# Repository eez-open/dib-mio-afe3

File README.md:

### Ownership and License
The contributors are listed in CONTRIB.TXT.

Licenses | OSHWA UID
--|--
 | 

### Overview

The [EEZ DIB](https://github.com/eez-open/modular-psu) 4-channel Hi-voltage/Hi-current AFE for [MIO168](https://github.com/eez-open/dib-mio168) module with two isolated inputs for voltage and current measurements.

### Feature list
* [ADS131E04](https://www.ti.com/product/ADS131E04) 24-bit 4-channel simultaneous sampling ADC with SPI
* AIN#1: Hi-voltage isolated (floated) input featuring 2 measurement ranges (±50 V, ±450 V)
* AIN#2: Hi-current isolated (floated) input featuring 2 measurement ranges (±1 A, ±10 A)
* AIN#3: Hi-voltage input featuring 3 measurement ranges (±2.4 V, ±48 V, ±240 V)
* AIN#4: Hi-current input featuring 3 measurement ranges (±24 mA, ±1.2 A, ±10 A), share common GND with AIN#3
* Latching relays for lower continuous power consumption
* Fused current inputs
* On-board ±2.5 V low noise LDOs
* Optional external voltage reference
* Dimensions: 132 x 68.5 mm, 4-layer PCB

### r1B4 prototype 3D model

### KiCad project (v7 or newer)

* [AFE3 r1B4](https://github.com/eez-open/dib-mio-afe3/tree/master/EDA%20files/KiCad)

All symbols, footprints and 3D models used in the project can be found in the [EEZ-DIB Library](https://github.com/eez-open/eez-kicad-libraries) plugin for KiCad.

### Bill of materials

* [Download](https://github.com/eez-open/dib-mio-afe3/tree/master/EDA%20files/KiCad/bom/ibom.html) as raw file _Interactive BOM_ (ibom.html) and open it locally in your browser.

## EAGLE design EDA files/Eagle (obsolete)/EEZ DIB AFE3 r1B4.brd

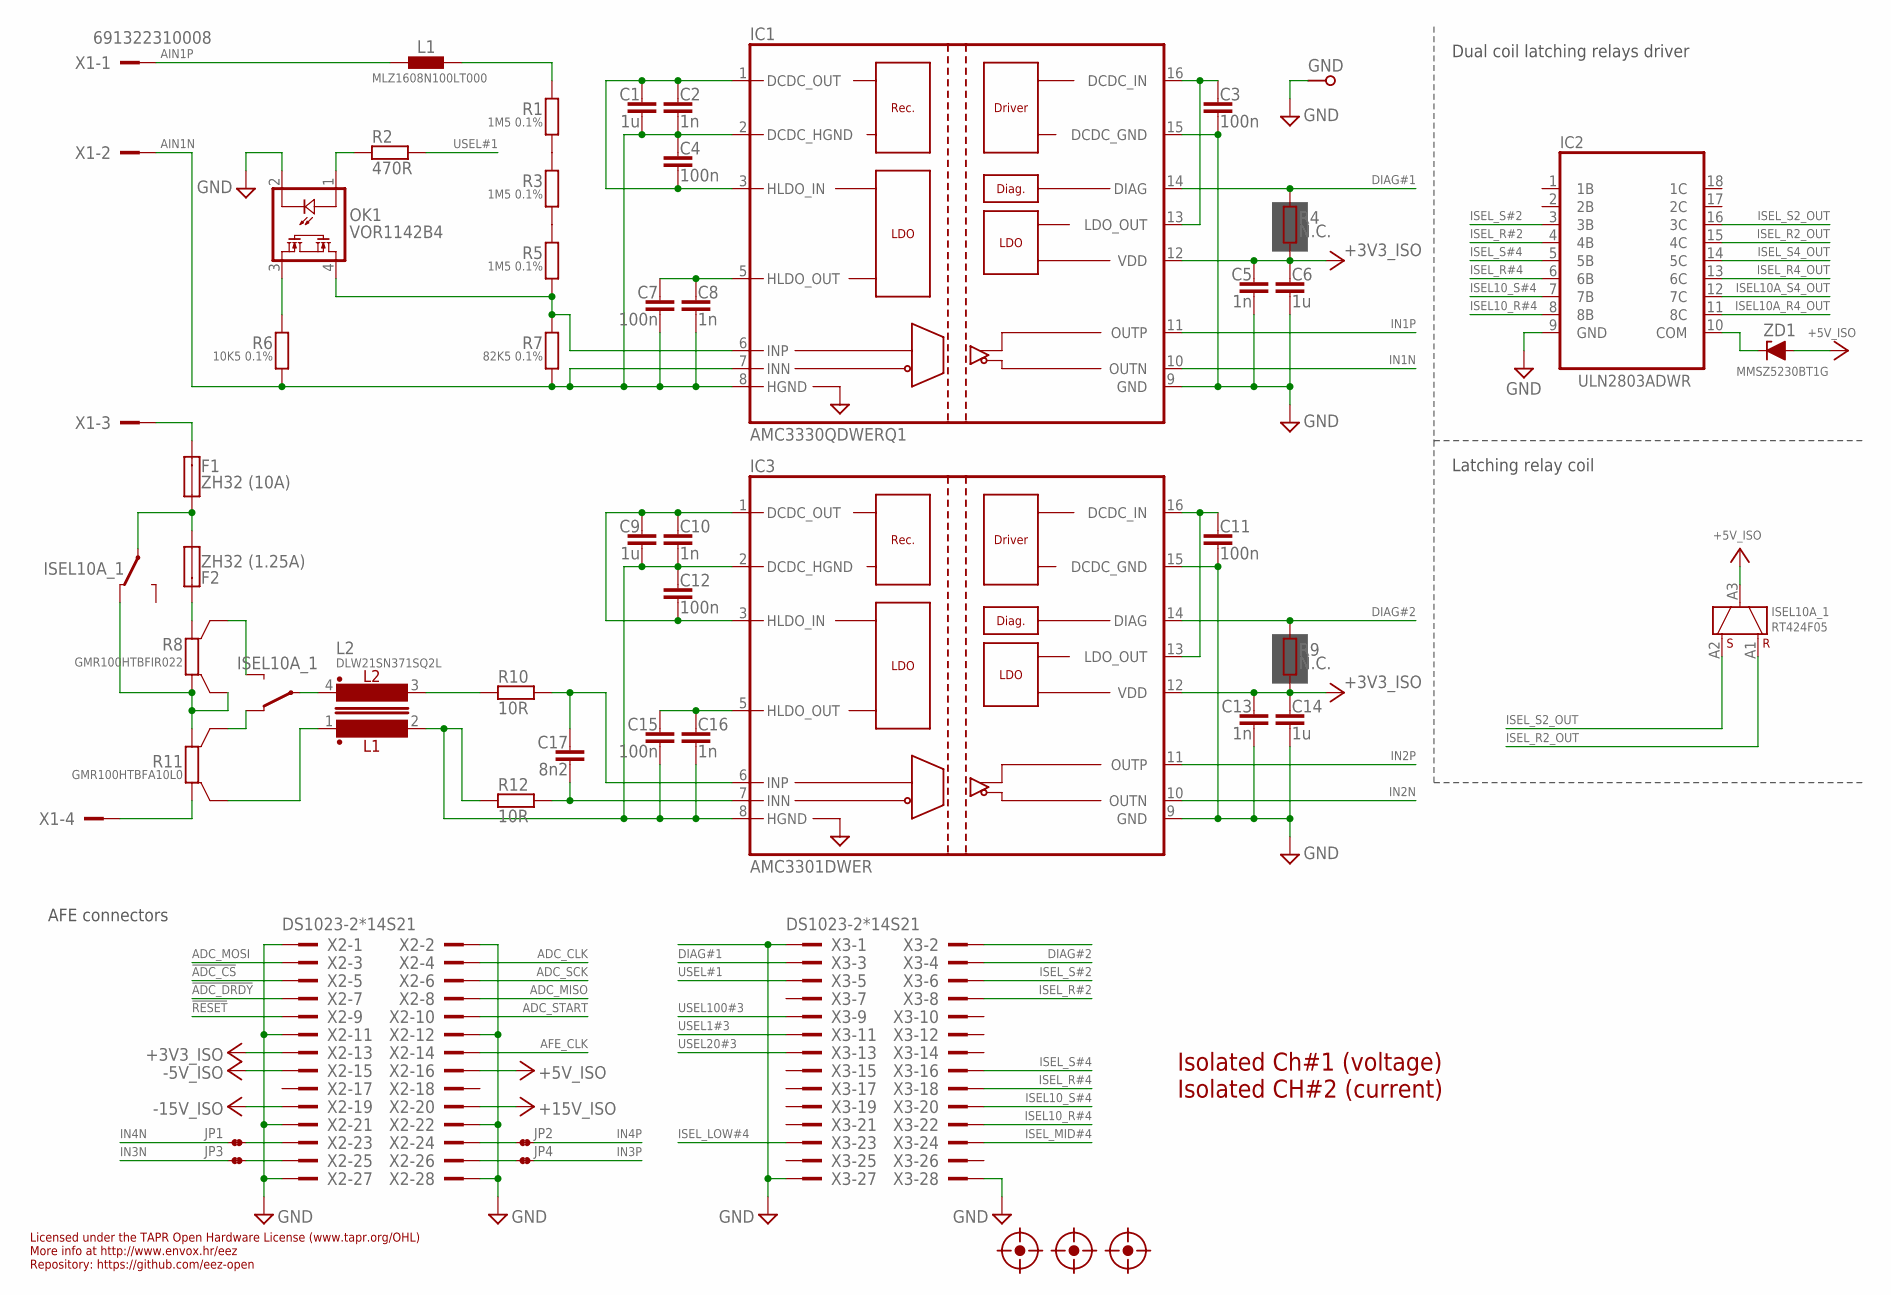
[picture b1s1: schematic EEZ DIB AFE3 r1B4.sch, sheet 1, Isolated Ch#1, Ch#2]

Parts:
C1, C9: 1u; C0603
C2, C10: 1n; C0603
C3, C4, C11, C12: 100n; C0603
C5, C8, C13, C16: 1n; C1206
C6, C14: 1u; C1206
C7, C15: 100n; C1206
C17: 8n2; C0603
F1: ZH32 (10A); ZH32
F2: ZH32 (1.25A); ZH32
FM1, FM2, FM3: FIDUCIAL_2; FIDUCIAL_DUAL
GND: PCB_TEST_TABSHIELD; PCB_SHIELD_TAB
IC1: AMC3330QDWERQ1; DW16
IC2: ULN2803ADWR; DW18_TEX-M
IC3: AMC3301DWER; DW16
ISEL10A_1: RT424F05; RT424FXX
JP1, JP2, JP3, JP4: JP2-NOCUT-0805; JP2-0805-NOCUT
L1: MLZ1608N100LT000; BEAD0603
L2: DLW21SN371SQ2L; MURATA_DLW21S
OK1: VOR1142B4; DIL4-SMD
R1, R3, R5: 1M5 0.1%; R1206
R2: 470R; R0805
R4, R9: N.C.; R0805
R6: 10K5 0.1%; R1206
R7: 82K5 0.1%; R1206
R8: GMR100HTBFIR022; R_2512-4WIRE
R10, R12: 10R; R0805
R11: GMR100HTBFA10L0; R_2512-4WIRE
X1: 691322310008
X2, X3: DS1023-2*14S21; TSW-114-07-F-D
ZD1: MMSZ5230BT1G; SOD123

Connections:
!ADC_CS: X2.5; also elsewhere on the board
!ADC_DRDY: X2.7; also elsewhere on the board
!RESET: X2.9; also elsewhere on the board
+3V3_ISO: C5.1, C6.1, C13.1, C14.1, IC1.12 (VDD), IC3.12 (VDD), R4.2, R9.2, X2.13; also elsewhere on the board
+5V_ISO: ISEL10A_1.A3 (COM), X2.16, ZD1.A; also elsewhere on the board
+15V_ISO: X2.20; also elsewhere on the board
-5V_ISO: X2.15; also elsewhere on the board
-15V_ISO: X2.19; also elsewhere on the board
ADC_CLK: X2.4; also elsewhere on the board
ADC_MISO: X2.8; also elsewhere on the board
ADC_MOSI: X2.3; also elsewhere on the board
ADC_SCK: X2.6; also elsewhere on the board
ADC_START: X2.10; also elsewhere on the board
AFE_CLK: X2.14
AIN1N: C1.2, C2.2, C4.1, C7.2, C8.2, IC1.2 (DCDC_HGND), IC1.7 (INN), IC1.8 (HGND), R6.1, R7.1, X1.2
AIN1P: L1.P$2 (2), X1.1
AIN2N: R11.1, X1.4
AIN2P: F1.2, X1.3
DIAG#1: IC1.14 (DIAG), R4.1, X3.3
DIAG#2: IC3.14 (DIAG), R9.1, X3.4
GND: C3.2, C5.2, C6.2, C11.2, C13.2, C14.2, GND.1, IC1.9 (GND), IC1.15 (DCDC_GND), IC2.9 (GND), IC3.9 (GND), IC3.15 (DCDC_GND), OK1.2 (C), X2.1, X2.2, X2.11, X2.12, X2.21, X2.22, X2.27, X2.28, X3.1, X3.27, X3.28; also elsewhere on the board
GNDI1: C9.2, C10.2, C12.1, C15.2, C16.2, IC3.2 (DCDC_HGND), IC3.8 (HGND), L2.2, R12.2
HI_FORCE+: ISEL10A_1.12 (NC), R8.1, R8.1S, R11.2
HI_SENSE+: ISEL10A_1.22 (NC), R11.2S
IN1N: IC1.10 (OUTN); also elsewhere on the board
IN1P: IC1.11 (OUTP); also elsewhere on the board
IN2N: IC3.10 (OUTN); also elsewhere on the board
IN2P: IC3.11 (OUTP); also elsewhere on the board
IN3N: JP3.1; also elsewhere on the board
IN3P: JP4.2; also elsewhere on the board
IN4N: JP1.1; also elsewhere on the board
IN4P: JP2.2; also elsewhere on the board
ISEL10A_R4_OUT: IC2.11 (8C); also elsewhere on the board
ISEL10A_S4_OUT: IC2.12 (7C); also elsewhere on the board
ISEL10_R#4: IC2.8 (8B), X3.22
ISEL10_S#4: IC2.7 (7B), X3.20
ISEL_LOW#4: X3.23; also elsewhere on the board
ISEL_MID#4: X3.24; also elsewhere on the board
ISEL_R2_OUT: IC2.15 (4C), ISEL10A_1.A1 (R)
ISEL_R4_OUT: IC2.13 (6C); also elsewhere on the board
ISEL_R#2: IC2.4 (4B), X3.8
ISEL_R#4: IC2.6 (6B), X3.18
ISEL_S2_OUT: IC2.16 (3C), ISEL10A_1.A2 (S)
ISEL_S4_OUT: IC2.14 (5C); also elsewhere on the board
ISEL_S#2: IC2.3 (3B), X3.6
ISEL_S#4: IC2.5 (5B), X3.16
LOW_SENSE+: ISEL10A_1.24 (NO), R8.2S
LO_FORCE-: F2.2, R8.2
unnamed: L1.P$1 (1), R1.2
unnamed: IC1.6 (INP), OK1.4 (S1), R5.1, R7.2
unnamed: R1.1, R3.2
unnamed: R3.1, R5.2
unnamed: OK1.3 (S2), R6.2
unnamed: C1.1, C2.1, C4.2, IC1.1 (DCDC_OUT), IC1.3 (HLDO_IN)
unnamed: C7.1, C8.1, IC1.5 (HLDO_OUT)
unnamed: C3.1, IC1.13 (LDO_OUT), IC1.16 (DCDC_IN)
unnamed: C17.1, IC3.6 (INP), R10.1
unnamed: C9.1, C10.1, C12.2, IC3.1 (DCDC_OUT), IC3.3 (HLDO_IN)
unnamed: C15.1, C16.1, IC3.5 (HLDO_OUT)
unnamed: C11.1, IC3.13 (LDO_OUT), IC3.16 (DCDC_IN)
unnamed: ISEL10A_1.21 (COM), L2.4
unnamed: F1.1, F2.1, ISEL10A_1.11 (COM)
unnamed: L2.1, R11.1S
unnamed: OK1.1 (A), R2.1
unnamed: L2.3, R10.2
unnamed: C17.2, IC3.7 (INN), R12.1
unnamed: IC2.10 (COM), ZD1.C
unnamed: JP1.2, X2.23
unnamed: JP3.2, X2.25
unnamed: JP2.1, X2.24
unnamed: JP4.1, X2.26
USEL1#3: X3.11; also elsewhere on the board
USEL20#3: X3.13; also elsewhere on the board
USEL100#3: X3.9; also elsewhere on the board
USEL#1: R2.2, X3.5

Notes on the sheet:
Licensed under the TAPR Open Hardware License (www.tapr.org/OHL)
Repository: https://github.com/eez-open
More info at http://www.envox.hr/eez
Isolated Ch#1 (voltage) Isolated CH#2 (current)
AFE connectors
Dual coil latching relays driver
Latching relay coil

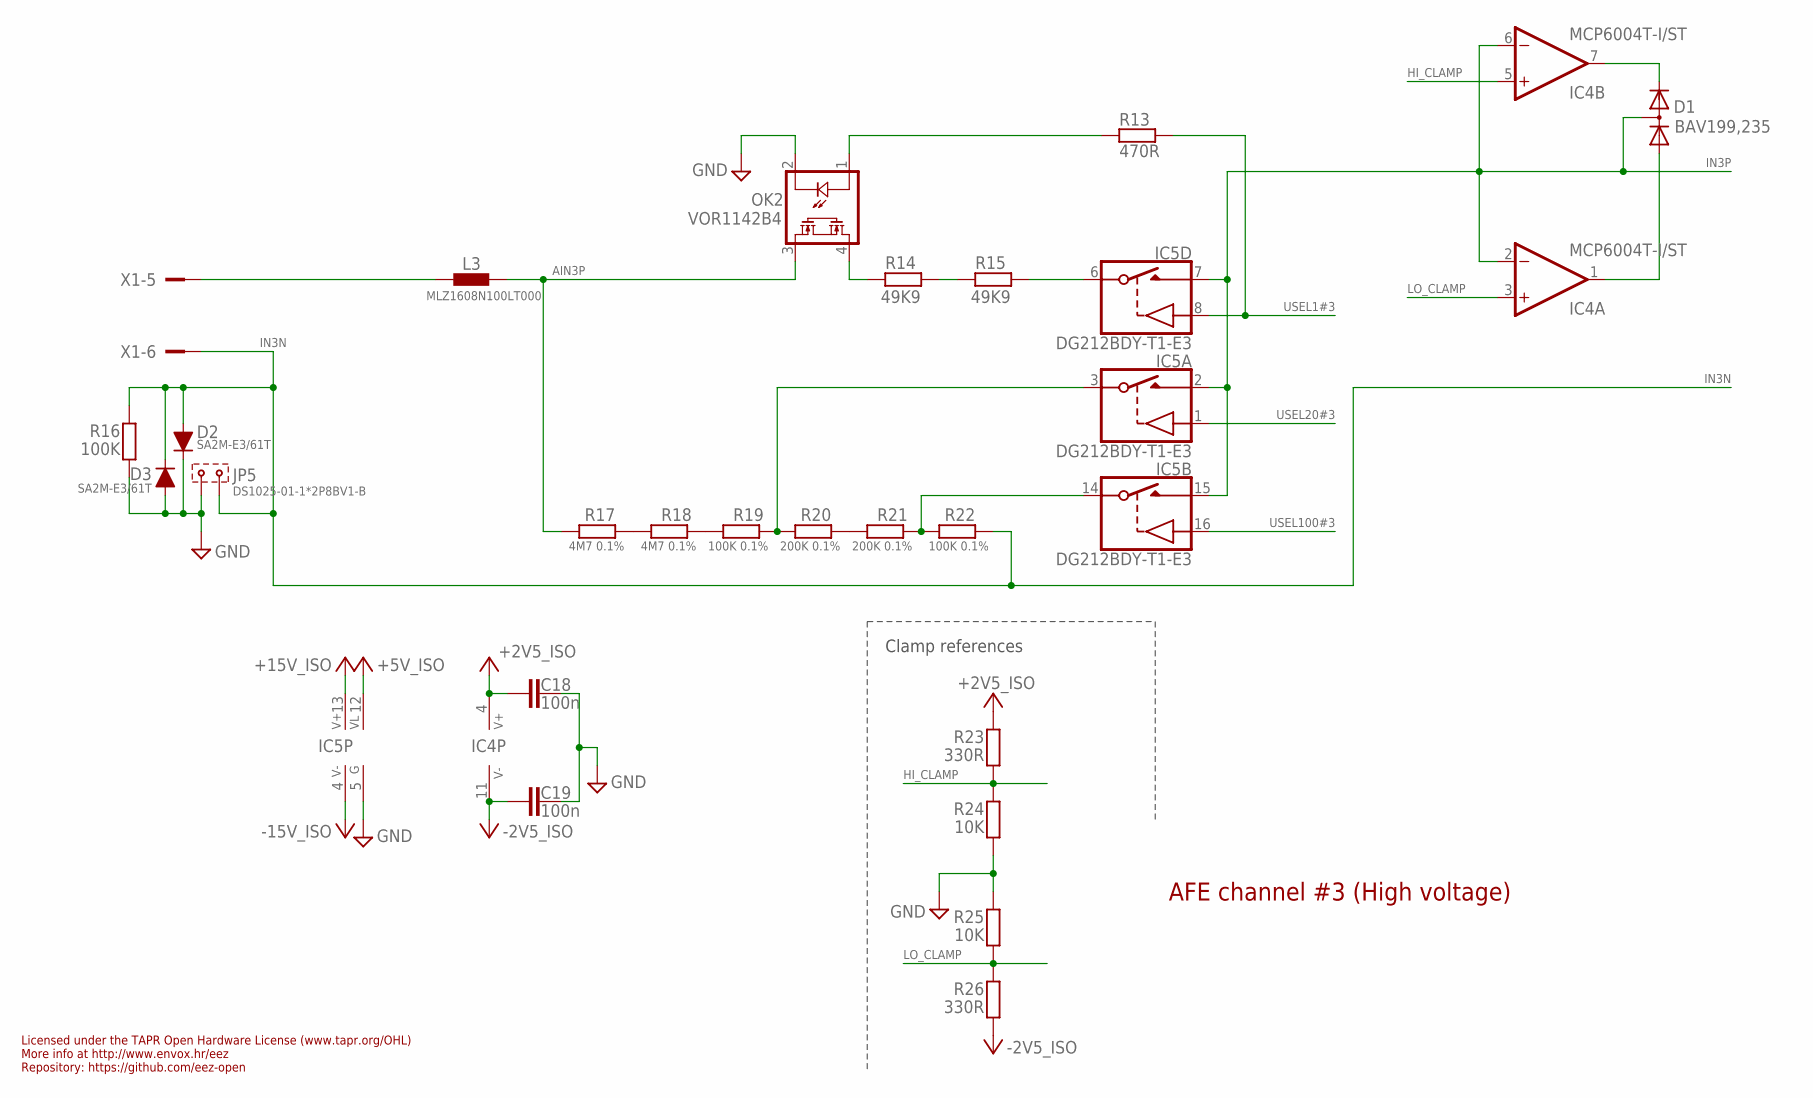
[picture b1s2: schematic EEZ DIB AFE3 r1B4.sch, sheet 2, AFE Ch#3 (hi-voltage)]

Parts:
C18, C19: 100n; C0603
D1: BAV199,235; SOT23
D2, D3: SA2M-E3/61T; SMA_NARROW
IC4: MCP6004T-I/ST; PW(R-PDSO-G14)
IC5: DG212BDY-T1-E3; SO16
JP5: DS1025-01-1*2P8BV1-B; 2MM-2
L3: MLZ1608N100LT000; BEAD0603
OK2: VOR1142B4; DIL4-SMD
R13: 470R; R0805
R14, R15: 49K9; R1206
R16: 100K; R1206
R17, R18: 4M7 0.1%; R1206
R19, R22: 100K 0.1%; R1206
R20, R21: 200K 0.1%; R1206
R23, R26: 330R; R0805
R24, R25: 10K; R0805
X1: 691322310008

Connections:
+2V5_ISO: C18.2, IC4.4 (V+), R23.1; also elsewhere on the board
+5V_ISO: IC5.12 (VL); also elsewhere on the board
+15V_ISO: IC5.13 (V+); also elsewhere on the board
-2V5_ISO: C19.2, IC4.11 (V-), R26.2; also elsewhere on the board
-15V_ISO: IC5.4 (V-); also elsewhere on the board
AIN3/20: IC5.3 (S), R19.1, R20.2
AIN3P: L3.P$1 (1), OK2.3 (S2), R17.2
GND: C18.1, C19.1, D2.1 (C), D3.2 (A), IC5.5 (GND), JP5.2, OK2.2 (C), R16.1, R24.2, R25.1; also elsewhere on the board
HI_CLAMP: IC4.5 (+IN), R23.2, R24.1; also elsewhere on the board
IN3N: D2.2 (A), D3.1 (C), JP5.1, R16.2, R22.1, X1.6; also elsewhere on the board
IN3P: D1.3 (AC), IC4.2 (-IN), IC4.6 (-IN), IC5.2 (D), IC5.7 (D), IC5.15 (D); also elsewhere on the board
LO_CLAMP: IC4.3 (+IN), R25.2, R26.1; also elsewhere on the board
unnamed: L3.P$2 (2), X1.5
unnamed: OK2.4 (S1), R14.2
unnamed: IC5.14 (S), R21.1, R22.2
unnamed: IC5.6 (S), R15.1
unnamed: D1.2 (C), IC4.7 (OUT)
unnamed: D1.1 (A), IC4.1 (OUT)
unnamed: R14.1, R15.2
unnamed: R20.1, R21.2
unnamed: R18.1, R19.2
unnamed: R17.1, R18.2
unnamed: OK2.1 (A), R13.2
USEL1#3: IC5.8 (IN), R13.1; also elsewhere on the board
USEL20#3: IC5.1 (IN); also elsewhere on the board
USEL100#3: IC5.16 (IN); also elsewhere on the board

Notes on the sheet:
Licensed under the TAPR Open Hardware License (www.tapr.org/OHL)
Repository: https://github.com/eez-open
More info at http://www.envox.hr/eez
AFE channel #3 (High voltage)
Clamp references

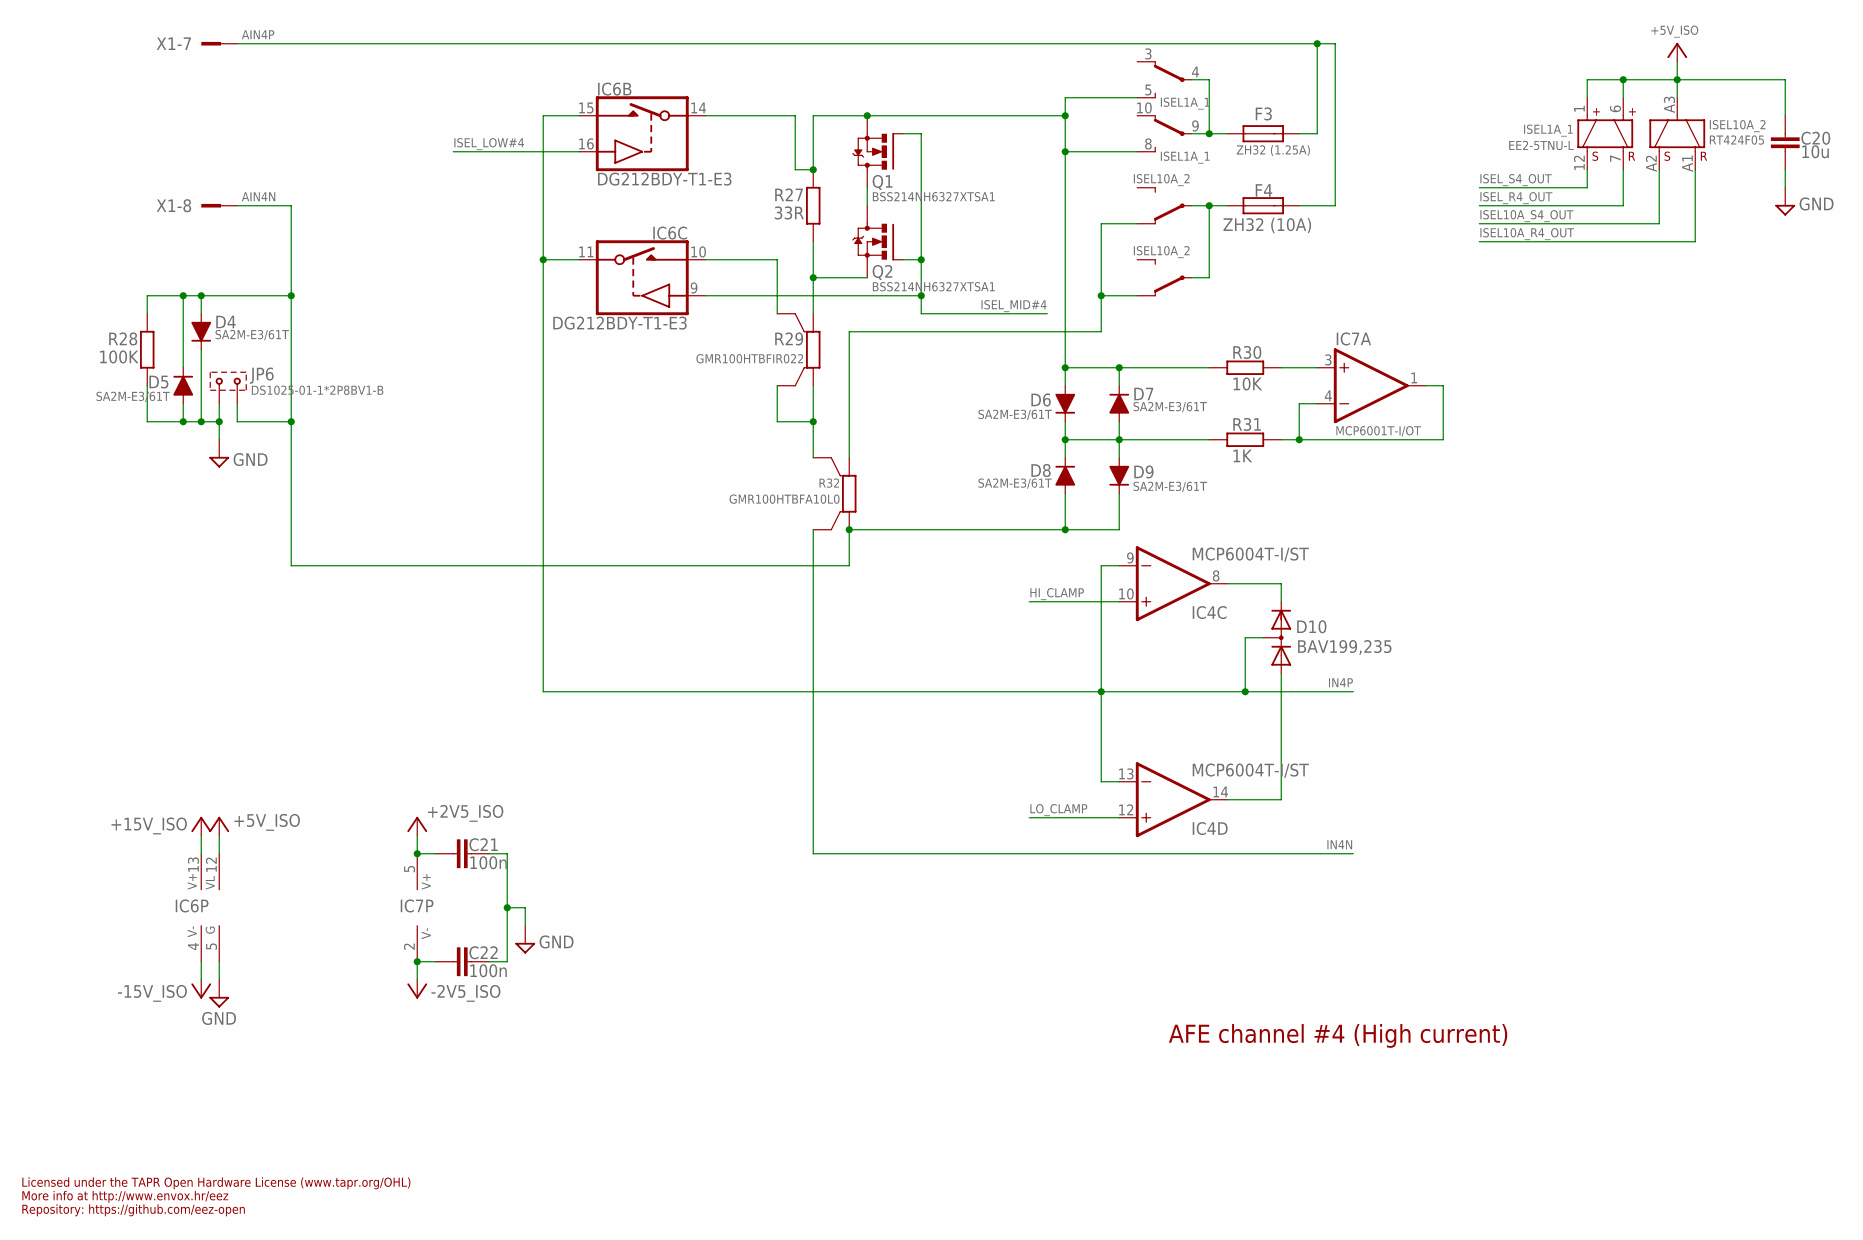
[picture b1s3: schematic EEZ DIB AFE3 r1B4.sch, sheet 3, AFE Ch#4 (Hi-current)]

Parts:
C20: 10u; C1206
C21, C22: 100n; C0603
D4, D5, D6, D7, D8, D9: SA2M-E3/61T; SMA_NARROW
D10: BAV199,235; SOT23
F3: ZH32 (1.25A); ZH32
F4: ZH32 (10A); ZH32
IC4: MCP6004T-I/ST; PW(R-PDSO-G14)
IC6: DG212BDY-T1-E3; SO16
IC7: MCP6001T-I/OT; DBV5
ISEL1A_1: EE2-5TNU-L; G6SK-2F
ISEL10A_2: RT424F05; RT424FXX
JP6: DS1025-01-1*2P8BV1-B; 2MM-2
Q1: BSS214NH6327XTSA1; SOT103P240X110-3N; MPN 2N7002-7-F
Q2: BSS214NH6327XTSA1; SOT103P240X110-3N
R27: 33R; R1206
R28: 100K; R1206
R29: GMR100HTBFIR022; R_2512-4WIRE
R30: 10K; R0805
R31: 1K; R0805
R32: GMR100HTBFA10L0; R_2512-4WIRE
X1: 691322310008

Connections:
+2V5_ISO: C21.2, IC7.5 (V+); also elsewhere on the board
+5V_ISO: C20.1, IC6.12 (VL), ISEL1A_1.1 (S+), ISEL1A_1.6 (R+), ISEL10A_2.A3 (COM); also elsewhere on the board
+15V_ISO: IC6.13 (V+); also elsewhere on the board
-2V5_ISO: C22.2, IC7.2 (V-); also elsewhere on the board
-15V_ISO: IC6.4 (V-); also elsewhere on the board
AIN4N: D4.2 (A), D5.1 (C), D8.2 (A), D9.1 (C), JP6.1, R28.2, R32.1, X1.8
AIN4P: F3.2, F4.2, X1.7
AIN4P_FUSED: F3.1, ISEL1A_1.4 (COM), ISEL1A_1.9 (COM)
GND: C20.2, C21.1, C22.1, D4.1 (C), D5.2 (A), IC6.5 (GND), JP6.2, R28.1; also elsewhere on the board
HI_CLAMP: IC4.10 (+IN); also elsewhere on the board
HI_CURR#1: ISEL10A_2.12 (NC), ISEL10A_2.22 (NC), R32.2
IN4N: R32.1S; also elsewhere on the board
IN4P: D10.3 (AC), IC4.9 (-IN), IC4.13 (-IN), IC6.11 (S), IC6.15 (D); also elsewhere on the board
ISEL10A_R4_OUT: ISEL10A_2.A1 (R); also elsewhere on the board
ISEL10A_S4_OUT: ISEL10A_2.A2 (S); also elsewhere on the board
ISEL_LOW#4: IC6.16 (IN); also elsewhere on the board
ISEL_MID#4: IC6.9 (IN), Q1.1 (G), Q2.1 (G); also elsewhere on the board
ISEL_R4_OUT: ISEL1A_1.7 (R-); also elsewhere on the board
ISEL_S4_OUT: ISEL1A_1.12 (S-); also elsewhere on the board
LO_CLAMP: IC4.12 (+IN); also elsewhere on the board
unnamed: R29.1, R29.1S, R32.2S
unnamed: IC6.10 (D), R29.2S
unnamed: F4.1, ISEL10A_2.11 (COM), ISEL10A_2.21 (COM)
unnamed: Q1.3 (D), Q2.3 (D)
unnamed: Q2.2 (S), R27.1, R29.2
unnamed: D6.1 (C), D7.2 (A), D8.1 (C), D9.2 (A), R31.2
unnamed: D6.2 (A), D7.1 (C), IC6.14 (S), ISEL1A_1.5 (NO), ISEL1A_1.8 (NO), Q1.2 (S), R27.2, R30.2
unnamed: IC7.1 (OUT), IC7.4 (-IN), R31.1
unnamed: IC7.3 (+IN), R30.1
unnamed: D10.2 (C), IC4.8 (OUT)
unnamed: D10.1 (A), IC4.14 (OUT)

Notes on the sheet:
Licensed under the TAPR Open Hardware License (www.tapr.org/OHL)
Repository: https://github.com/eez-open
More info at http://www.envox.hr/eez
AFE channel #4 (High current)

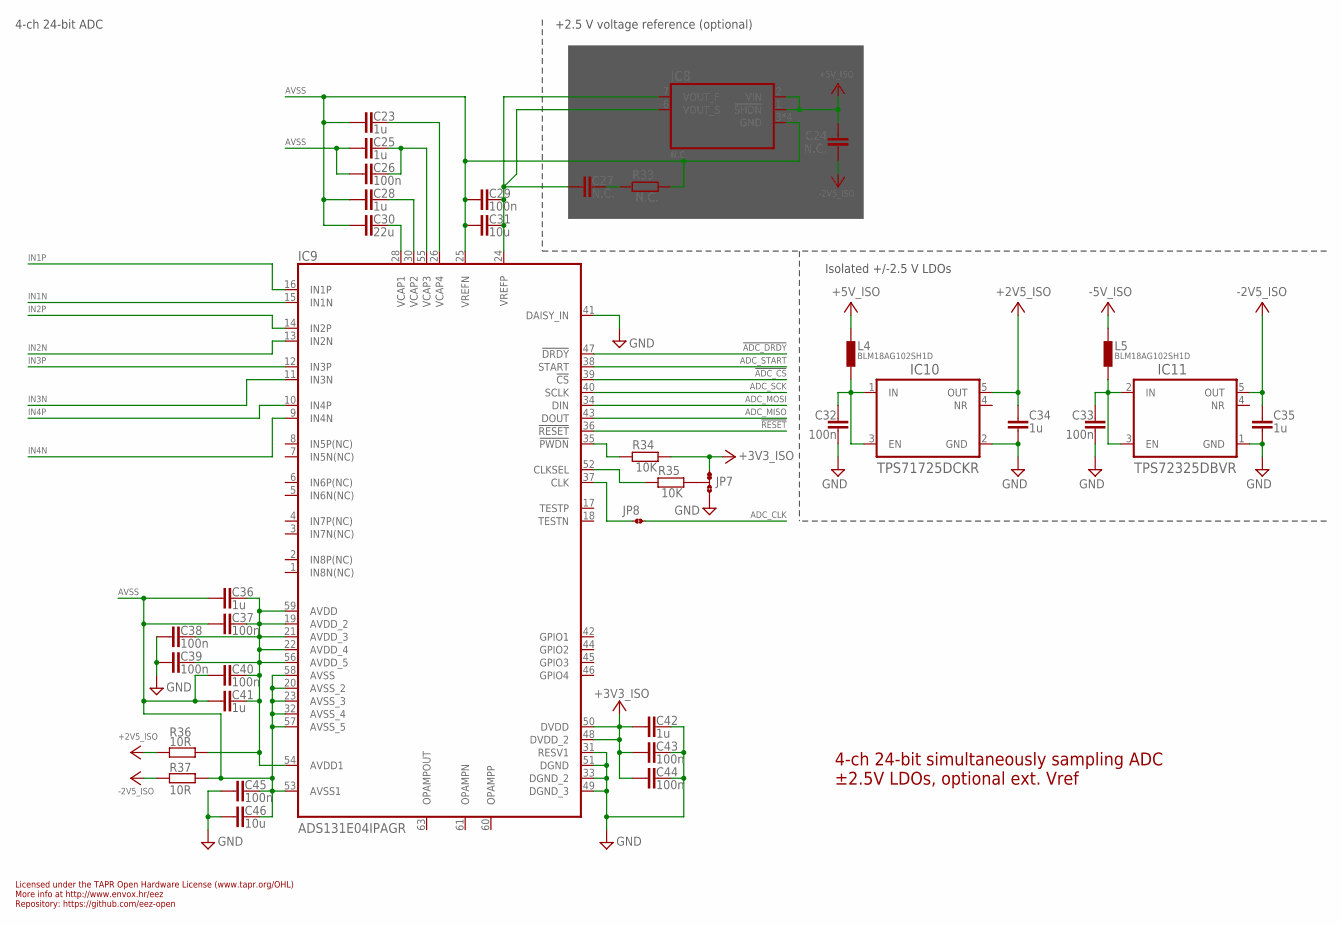
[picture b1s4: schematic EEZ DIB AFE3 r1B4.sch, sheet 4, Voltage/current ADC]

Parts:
C23, C25, C28, C34, C35, C36, C41, C42: 1u; C0805
C24, C27: N.C.; C1206
C26, C29, C32, C33, C37, C38, C39, C40, C43, C44, C45: 100n; C0603
C30: 22u; C1206
C31, C46: 10u; C1206
IC8: N.C.; MSOP-8_MS_LIT
IC9: ADS131E04IPAGR; PAG64
IC10: TPS71725DCKR; DCK5
IC11: TPS72325DBVR; DBV5
JP7: JP3-CUT-0805-ROTATED; JP3-0805-CUT2
JP8: JP2-CUT-0805; R_0805
L4, L5: BLM18AG102SH1D; BEAD0603
R33: N.C.; R0805
R34, R35: 10K; R0805
R36, R37: 10R; R0805

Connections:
!ADC_CS: IC9.39 (!CS); also elsewhere on the board
!ADC_DRDY: IC9.47 (!DRDY); also elsewhere on the board
!RESET: IC9.36 (!RESET); also elsewhere on the board
+2V5_ADC: C36.2, C37.1, C38.1, C39.1, C40.1, C41.2, IC9.19 (AVDD_2), IC9.21 (AVDD_3), IC9.22 (AVDD_4), IC9.54 (AVDD1), IC9.56 (AVDD_5), IC9.59 (AVDD), R36.2
+2V5_ISO: C34.2, IC10.5 (OUT), R36.1; also elsewhere on the board
+3V3_ISO: C42.1, C43.2, C44.2, IC9.48 (DVDD_2), IC9.50 (DVDD), JP7.NC, R34.2; also elsewhere on the board
+5V_ISO: C24.1, IC8.1 (!SHDN), IC8.2 (VIN), L4.P$2 (2); also elsewhere on the board
-2V5_ISO: C24.2, C35.2, IC11.5 (OUT), R37.2; also elsewhere on the board
-5V_ISO: L5.P$2 (2); also elsewhere on the board
ADC_CLK: JP8.1; also elsewhere on the board
ADC_MISO: IC9.43 (DOUT); also elsewhere on the board
ADC_MOSI: IC9.34 (DIN); also elsewhere on the board
ADC_SCK: IC9.40 (SCLK); also elsewhere on the board
ADC_START: IC9.38 (START); also elsewhere on the board
AVSS: C23.1, C25.1, C26.2, C28.1, C29.2, C30.1, C31.2, C36.1, C37.2, C40.2, C41.1, C45.1, C46.1, IC8.3 (GND), IC8.4 (GND), IC8.5 (GND), IC8.8 (GND), IC9.20 (AVSS_2), IC9.23 (AVSS_3), IC9.25 (VREFN), IC9.32 (AVSS_4), IC9.53 (AVSS1), IC9.57 (AVSS_5), IC9.58 (AVSS), R33.2, R37.1
GND: C32.2, C33.2, C34.1, C35.1, C38.2, C39.2, C42.2, C43.1, C44.1, C45.2, C46.2, IC9.31 (RESV1), IC9.33 (DGND_2), IC9.41 (DAISY_IN), IC9.49 (DGND_3), IC9.51 (DGND), IC10.2 (GND), IC11.1 (GND), JP7.NO; also elsewhere on the board
IN1N: IC9.15 (IN1N); also elsewhere on the board
IN1P: IC9.16 (IN1P); also elsewhere on the board
IN2N: IC9.13 (IN2N); also elsewhere on the board
IN2P: IC9.14 (IN2P); also elsewhere on the board
IN3N: IC9.11 (IN3N); also elsewhere on the board
IN3P: IC9.12 (IN3P); also elsewhere on the board
IN4N: IC9.9 (IN4N); also elsewhere on the board
IN4P: IC9.10 (IN4P); also elsewhere on the board
unnamed: IC9.52 (CLKSEL), R35.1
unnamed: C32.1, IC10.1 (IN), IC10.3 (EN), L4.P$1 (1)
unnamed: C33.1, IC11.2 (IN), IC11.3 (EN), L5.P$1 (1)
unnamed: JP7.COM, R35.2
unnamed: C30.2, IC9.28 (VCAP1)
unnamed: C28.2, IC9.30 (VCAP2)
unnamed: C25.2, C26.1, IC9.55 (VCAP3)
unnamed: C23.2, IC9.26 (VCAP4)
unnamed: IC9.37 (CLK), JP8.2
unnamed: IC9.35 (!PWDN), R34.1
unnamed: C27.2, R33.1
VREFP: C27.1, C29.1, C31.1, IC8.6 (VOUT_S), IC8.7 (VOUT_F), IC9.24 (VREFP)

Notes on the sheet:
Licensed under the TAPR Open Hardware License (www.tapr.org/OHL)
Repository: https://github.com/eez-open
More info at http://www.envox.hr/eez
4-ch 24-bit simultaneously sampling ADC ±2.5V LDOs, optional ext. Vref
4-ch 24-bit ADC
+2.5 V voltage reference (optional)
Isolated +/-2.5 V LDOs

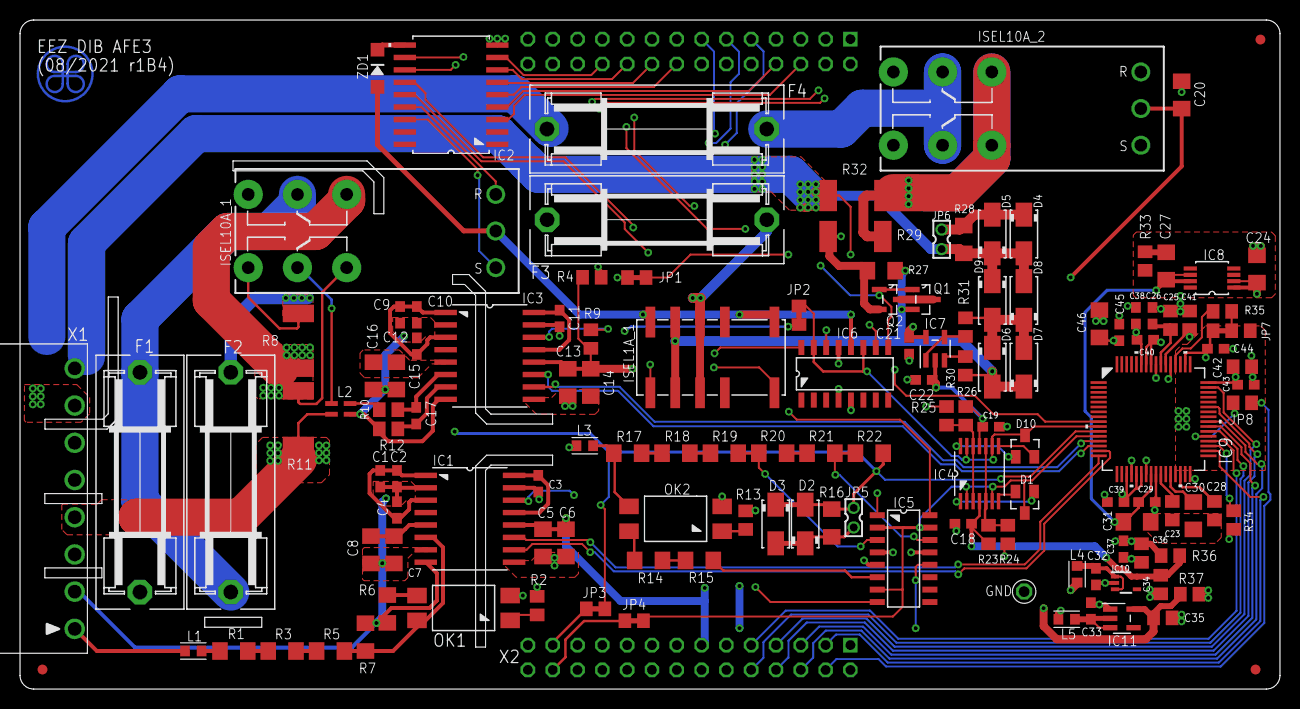
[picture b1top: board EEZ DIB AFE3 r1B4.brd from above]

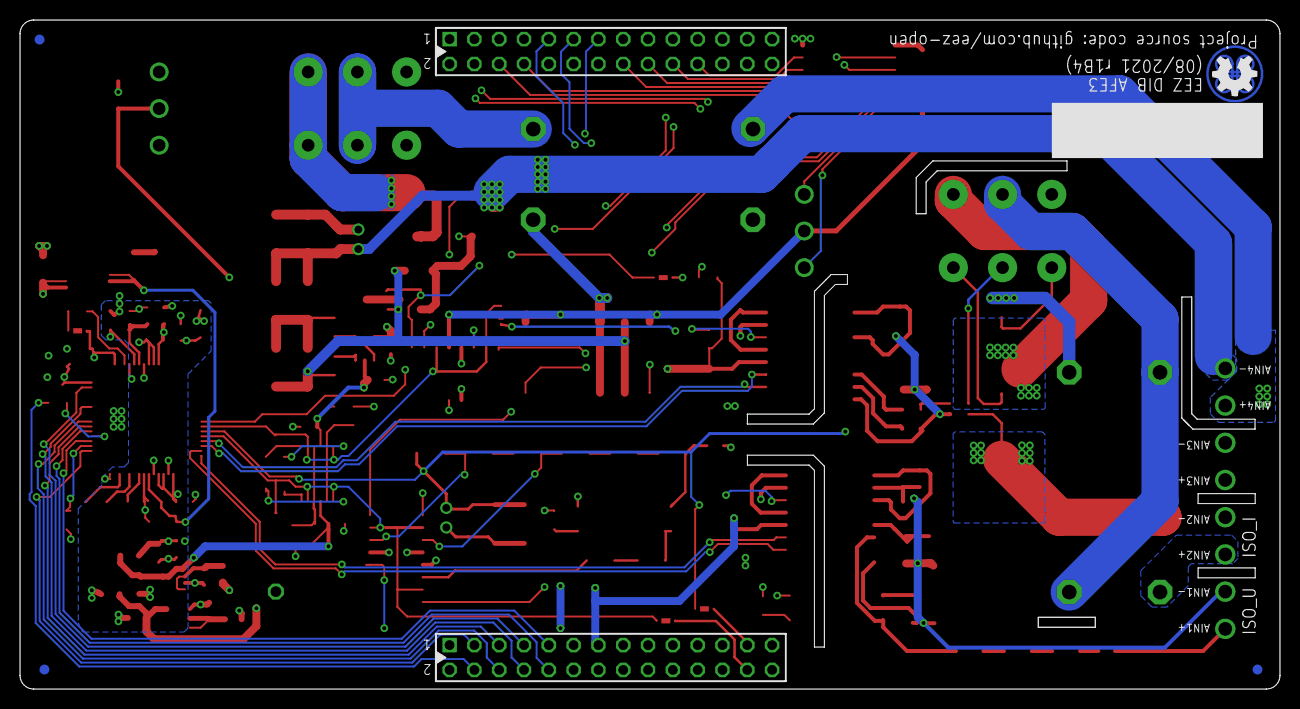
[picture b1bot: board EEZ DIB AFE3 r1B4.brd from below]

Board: 4 copper layers, 129.0 x 68.5 mm, 137 parts (2 on the bottom side), 120 nets.

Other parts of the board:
EEZ_SIGNATURE: SIGNATURESMALL; SIGNATURE_5MM

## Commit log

2021-03-31 README.md added
2021-03-31 cleanup
2021-05-07 r1B2 (removed RC from ADC inputs)
2021-05-07 Renaming .sch page files
2021-05-14 New Rsense values, PCB layout adjustment for mid range Rsense
2021-05-14 R30 value corrected
2021-09-29 Gerbers, BOM, schematics update
2021-10-08 OSHWA UID
2024-01-19 #6, #7 (r1B3 KiCad)
2024-01-19 Revert "#6, #7 (r1B3 KiCad)"
    This reverts commit 52033645fb07d7287d4da63e50f45c25d80231af.
2024-01-19 Migration to KiCad
2024-01-20 PCB preview correction

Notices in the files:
parts and their libraries:
EEZ_DIB: This work is licensed under the TAPR Open Hardware License.
